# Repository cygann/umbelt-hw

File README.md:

# umbelt-hw

This repo contains the hardware files for Umbelt: a sensory substitution belt
for everyday use. Designed to be worn around the waist underneath any belt,
Umbelt doesn't compromise on function or style. The name Umbelt (pronounced
"oom-belt") is a pun on the German word umwelt, used in English to describe an
organism's sensory environment and perceptions.

Sensory substitution "is a change of the characteristics of one sensory modality
into stimuli of another sensory modality."
([Wikipedia](https://en.wikipedia.org/wiki/Sensory_substitution))
This means that sensory modalities which are not otherwise accessible to an
individual can be recreated using haptic feedback on the waist. This includes
ordinary sensory functions for prosthetic purposes as well as sensory
information that is beyond typical human senses, such as electromagnetic
radiation outside the visible spectrum, the Earth's magnetic field, time,
physical proximity, velocity, or any other information in the computing world.

The initial configuration to try is the compass feature. This maps one's
absolute orientation to the waist by always indicating where north is whenever
the wearer's orientation changes. After wearing this for a while, the wearer
experiences subtle changes in spatial perception. It becomes more natural to
think in terms of absolute orientation, and separate locations become better
integrated into a larger, more continuous sense of space.

# Hardware Design

Umbelt is designed as an assembly of two printed circuits: a rigid printed
circuit board (PCB) and a flexible printed circuit (FPC). The board mounts all
of the electronic components: the microcontroller, power regulators, 13 motor
drivers, integrated sensors (magnetometer, accelerometer/gyroscope, and
microphone), and connectors. The flex PC connects to the board and wraps around
the wearer's waist, providing electrical connections to 12 of the 13 motors.

The Microcontroller is a Raytac MDBT50Q-1MV2 module based on the Nordic nRF52840
bluetooth microcontroller. This bluetooth connection enables phone-based
configuration of Umbelt. A Sparkfun/Adafruit-style Qwiic expansion connector
allows for the daisy-chaining of additional I2C sensors to Umbelt.

Schematics and layout were designed with KiCad version 5.1.10.

Schematics can be found [here](umbelt-board/umbelt-board.pdf).

# Related Repositories

[Software](https://github.com/cygann/umbelt-sw). Haptic effects, sensor
libraries, and user programs.

[Bootloader](https://github.com/cygann/Adafruit_nRF52_Bootloader). This
is a modified version of the Adafruit Feather nRF52840 Sense bootloader, and
that target is to be used when compiling and flashing.

# License

_Creators' note: The aim of this license is to be semi-permissive: Umbelt may
be used in larger projects under different licenses but Umbelt itself and
modifications to it must be open-source under the same license. Refer to license
text for specifics._

Copyright Natalie Cygan and Matthew Pauly 2021.

This source describes Open Hardware and is licensed under the CERN-OHL-W v2 or
later

You may redistribute and modify this documentation and make products
using it under the terms of the CERN-OHL-W v2 (https://ohwr.org/cernohl).
This documentation is distributed WITHOUT ANY EXPRESS OR IMPLIED
WARRANTY, INCLUDING OF MERCHANTABILITY, SATISFACTORY QUALITY
AND FITNESS FOR A PARTICULAR PURPOSE. Please see the CERN-OHL-W v2
for applicable conditions.

Source location: https://github.com/cygann/umbelt-hw

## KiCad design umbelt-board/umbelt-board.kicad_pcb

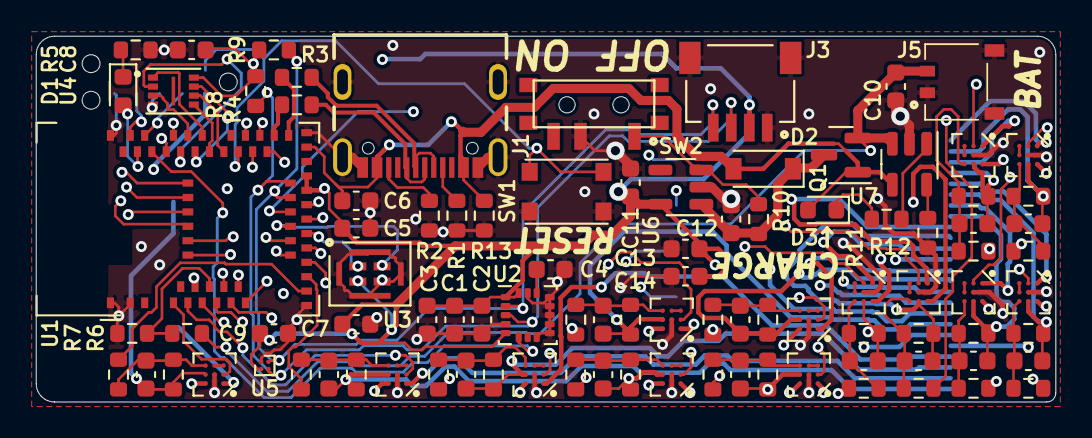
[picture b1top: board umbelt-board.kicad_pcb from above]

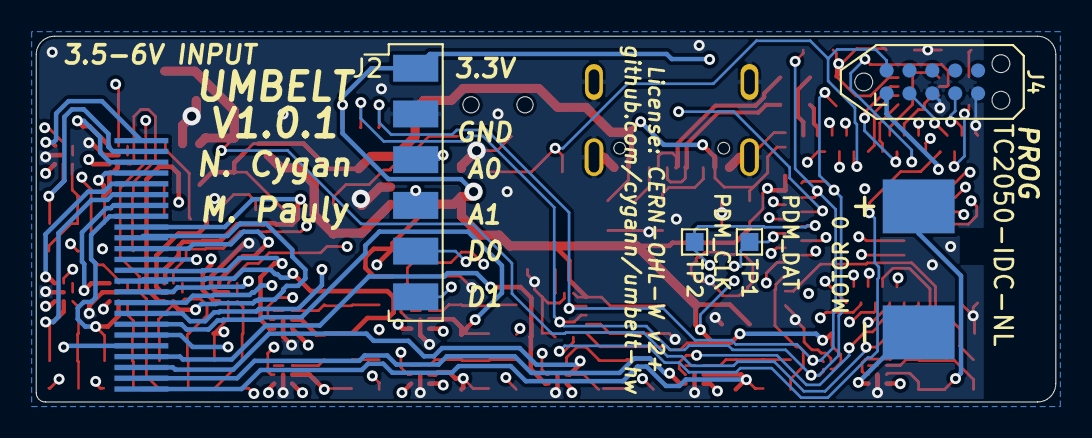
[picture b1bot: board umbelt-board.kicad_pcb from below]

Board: 4 copper layers, 56.6 x 20.3 mm, 101 parts (6 on the bottom side), 115 nets.

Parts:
C1, C7, C8, C14: 0.1uF; C_0603_1608Metric
C2, C15, C16, C17, C18, C19, C20, C21, C22, C23, C24, C25, C26, C27: 4.7nF; C_0603_1608Metric
C3, C9, C13: 2.2uF; C_0603_1608Metric
C4: 0.47uF; C_0603_1608Metric
C5, C6, C10, C11, C12: 10uF; C_0603_1608Metric
D1: SML-D12M1W; LED_0603_1608Metric
D2: MBR0520; D_SOD-123
D3: SML-D12D1W; LED_0603_1608Metric
J1: USB4105-GF-A; GCT_USB4105-GF-A
J2: Conn_01x06; PinHeader_1x06_P2.54mm_Right_Angle_SMD
J3: SM04B-SRSS-TB; JST_SM04B-SRSS-TB(LF)(SN)
J4: TC2050-IDC-NL; Tag-Connect_TC2050-IDC-NL_2x05_P1.27mm_Vertical
J5: BM02B-ACHLKS
J6: Conn_Flex_Motor
J7: Conn_Indiv_Motor
Q1: AO3415A; SOT-23
R1, R2: 5.1k; R_0603_1608Metric
R3, R4: 22; R_0603_1608Metric
R5, R11: 1k; R_0603_1608Metric
R6, R7, R10, R13, R14, R15, R16, R17, R18, R19, R20, R21, R22, R23, R24, R25, R26, R27, R28, R29, R30, R31, R32, R33, R34, R35, R36, R37, R38, R39: 100k; R_0603_1608Metric
R8, R9: 2.2k; R_0603_1608Metric
R12: 10k; R_0603_1608Metric
SW1: KMR231NG-ULC-LFS; KMR2-NG
SW2: CUS-12TB; CUS-12B
TP1: PDM_DAT; TestPoint_Pad_1.0x1.0mm
TP2: PDM_CLK; TestPoint_Pad_1.0x1.0mm
U1: MDBT50Q-1MV2; Raytac_MDBT50Q
U2: ICM-20608; LGA-16_3x3mm_P0.5mm_LayoutBorder3x5y
U3: SPK0641HT4H-1; Knowles_SPK0641HT4H-1
U4: MX25R1635FZUIL0; USON-8_2x3
U5: MMC5633NJL; WLP-4_0.86x0.86mm_P0.4mm
U6: AP7366-33W5; SOT-23-5
U7: MCP73832-2ACI_MC‎; SOT-23-5
U8, U9, U10, U11, U12, U13, U14, U15, U16, U17, U18, U19, U20: DRV8601; BGA-8_3x3_2.1x2.1mm_TI_ZQV

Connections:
+3V3: C1.1, C2.2, C3.1, C5.1, C7.1, C8.1, C9.1, C11.1, C13.1, C14.1, J2.1, J3.2, J4.1, R8.1, R9.1, U1.28, U1.30, U2.1, U2.5, U2.16, U3.4, U4.8, U5.B1, U6.5, U8.A3, U9.A3, U10.A3, U11.A3, U12.A3, U13.A3, U14.A3, U15.A3, U16.A3, U17.A3, U18.A3, U19.A3, U20.A3
/A0: J2.5, U1.10
/A1: J2.6, U1.11
/ACC_IRQ: U1.50, U2.6
/D0: J2.3, U1.48
/D1: J2.4, U1.49
/D+: J1.A6, J1.B6, R4.1
/D-: J1.A7, J1.B7, R3.1
/LED: D1.2, U1.52
/MOTOR_EN_0: U1.4, U20.B1
/MOTOR_EN_1: U1.6, U8.B1
/MOTOR_EN_2: U1.8, U9.B1
/MOTOR_EN_3: U1.12, U10.B1
/MOTOR_EN_4: U1.14, U11.B1
/MOTOR_EN_5: U1.13, U12.B1
/MOTOR_EN_6: U1.7, U13.B1
/MOTOR_EN_7: U1.56, U14.B1
/MOTOR_EN_8: U1.57, U15.B1
/MOTOR_EN_9: U1.58, U16.B1
/MOTOR_EN_10: U1.59, U17.B1
/MOTOR_EN_11: U1.60, U18.B1
/MOTOR_EN_12: U1.61, U19.B1
/MOTOR_PWM_0: R38.1, U1.16
/MOTOR_PWM_1: R14.1, U1.17
/MOTOR_PWM_2: R16.1, U1.18
/MOTOR_PWM_3: R18.1, U1.19
/MOTOR_PWM_4: R20.1, U1.20
/MOTOR_PWM_5: R22.1, U1.21
/MOTOR_PWM_6: R24.1, U1.24
/MOTOR_PWM_7: R26.1, U1.25
/MOTOR_PWM_8: R28.1, U1.26
/MOTOR_PWM_9: R30.1, U1.36
/MOTOR_PWM_10: R32.1, U1.37
/MOTOR_PWM_11: R34.1, U1.38
/MOTOR_PWM_12: R36.1, U1.39
/PDM_CLK: TP2.1, U1.23, U3.2
/PDM_DAT: TP1.1, U1.22, U3.1
/QSPI_CS: U1.44, U4.1
/QSPI_DATA0: U1.43, U4.5
/QSPI_DATA1: U1.47, U4.2
/QSPI_DATA2: U1.46, U4.3
/QSPI_DATA3: U1.45, U4.7
/QSPI_SCK: U1.42, U4.6
/REGIN: C12.2, D2.1, Q1.3, R10.1, U6.1
/RESET: J4.10, SW1.2, U1.40
/SCL: J3.4, R9.2, U1.27, U2.2, U5.A2
/SDA: J3.3, R8.2, U1.29, U2.3, U5.B2
/SWCLK: J4.4, U1.53
/SWDIO: J4.2, U1.51
/USBD+: R4.2, U1.35
/USBD-: R3.2, U1.34
/VDIV: R6.2, R7.1, U1.9
/motor_drivers/OUT+_0: C27.1, J7.1, R39.2, U20.B3
/motor_drivers/OUT+_1: C15.1, J6.1, R15.2, U8.B3
/motor_drivers/OUT+_2: C16.1, J6.3, R17.2, U9.B3
/motor_drivers/OUT+_3: C17.1, J6.5, R19.2, U10.B3
/motor_drivers/OUT+_4: C18.1, J6.7, R21.2, U11.B3
/motor_drivers/OUT+_5: C19.1, J6.9, R23.2, U12.B3
/motor_drivers/OUT+_6: C20.1, J6.11, R25.2, U13.B3
/motor_drivers/OUT+_7: C21.1, J6.13, R27.2, U14.B3
/motor_drivers/OUT+_8: C22.1, J6.15, R29.2, U15.B3
/motor_drivers/OUT+_9: C23.1, J6.17, R31.2, U16.B3
/motor_drivers/OUT+_10: C24.1, J6.19, R33.2, U17.B3
/motor_drivers/OUT+_11: C25.1, J6.21, R35.2, U18.B3
/motor_drivers/OUT+_12: C26.1, J6.23, R37.2, U19.B3
/motor_drivers/OUT-_0: J7.2, U20.A1
/motor_drivers/OUT-_1: J6.2, U8.A1
/motor_drivers/OUT-_2: J6.4, U9.A1
/motor_drivers/OUT-_3: J6.6, U10.A1
/motor_drivers/OUT-_4: J6.8, U11.A1
/motor_drivers/OUT-_5: J6.10, U12.A1
/motor_drivers/OUT-_6: J6.12, U13.A1
/motor_drivers/OUT-_7: J6.14, U14.A1
/motor_drivers/OUT-_8: J6.16, U15.A1
/motor_drivers/OUT-_9: J6.18, U16.A1
/motor_drivers/OUT-_10: J6.20, U17.A1
/motor_drivers/OUT-_11: J6.22, U18.A1
/motor_drivers/OUT-_12: J6.24, U19.A1
GND: C1.2, C2.1, C3.2, C4.2, C5.2, C6.2, C7.2, C8.2, C9.2, C10.2, C11.2, C12.1, C13.2, C14.2, J1.A1, J1.A12, J1.B1, J1.B12, J1.S1, J2.2, J3.1, J3.S1, J4.3, J4.5, J5.1, J5.S1, R1.2, R2.2, R5.2, R7.2, R12.2, R13.2, SW1.1, SW2.2, U1.1, U1.2, U1.15, U1.33, U1.55, U2.4, U2.8, U2.9, U2.10, U2.11, U2.12, U2.13, U2.15, U3.3, U3.5, U3.6, U3.7, U3.8, U4.4, U5.A1, U6.2, U7.2, U8.B2, U9.B2, U10.B2, U11.B2, U12.B2, U13.B2, U14.B2, U15.B2, U16.B2, U17.B2, U18.B2, U19.B2, U20.B2
unnamed: C4.1, U2.14
unnamed: C15.2, R14.2, R15.1, U8.C3
unnamed: C16.2, R16.2, R17.1, U9.C3
unnamed: C17.2, R18.2, R19.1, U10.C3
unnamed: C18.2, R20.2, R21.1, U11.C3
unnamed: C19.2, R22.2, R23.1, U12.C3
unnamed: C20.2, R24.2, R25.1, U13.C3
unnamed: C21.2, R26.2, R27.1, U14.C3
unnamed: C22.2, R28.2, R29.1, U15.C3
unnamed: C23.2, R30.2, R31.1, U16.C3
unnamed: C24.2, R32.2, R33.1, U17.C3
unnamed: C25.2, R34.2, R35.1, U18.C3
unnamed: C26.2, R36.2, R37.1, U19.C3
unnamed: C27.2, R38.2, R39.1, U20.C3
unnamed: D1.1, R5.1
unnamed: D3.1, R11.1
unnamed: J1.A5, R1.1
unnamed: J1.B5, R2.1
unnamed: R10.2, SW2.1, U6.3
unnamed: R11.2, U7.1
unnamed: R12.1, U7.5
unnamed: U8.C1, U8.C2
unnamed: U9.C1, U9.C2
unnamed: U10.C1, U10.C2
unnamed: U11.C1, U11.C2
unnamed: U12.C1, U12.C2
unnamed: U13.C1, U13.C2
unnamed: U14.C1, U14.C2
unnamed: U15.C1, U15.C2
unnamed: U16.C1, U16.C2
unnamed: U17.C1, U17.C2
unnamed: U18.C1, U18.C2
unnamed: U19.C1, U19.C2
unnamed: U20.C1, U20.C2
VBAT: C10.1, J5.2, Q1.2, R6.1, U7.3
VBUS: C6.1, D2.2, D3.2, J1.A4, J1.A9, J1.B4, J1.B9, Q1.1, R13.1, U1.32, U7.4

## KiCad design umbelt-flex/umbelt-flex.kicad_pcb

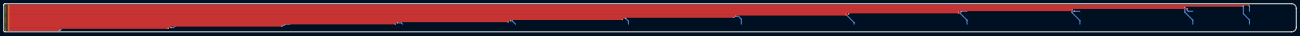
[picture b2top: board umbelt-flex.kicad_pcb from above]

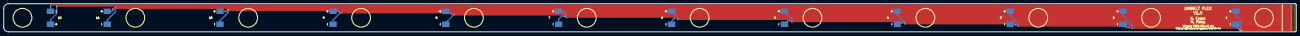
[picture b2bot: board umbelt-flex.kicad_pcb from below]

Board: 2 copper layers, 701.0 x 15.2 mm, 13 parts (12 on the bottom side), 24 nets.

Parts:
J1, J2, J3, J4, J5, J6, J7, J8, J9, J10, J11, J12: Conn_Indiv_Motor
J13: Conn_Flex_Motor

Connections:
/OUT+_1: J1.1, J13.1
/OUT+_2: J2.1, J13.3
/OUT+_3: J3.1, J13.5
/OUT+_4: J4.1, J13.7
/OUT+_5: J5.1, J13.9
/OUT+_6: J6.1, J13.11
/OUT+_7: J7.1, J13.13
/OUT+_8: J8.1, J13.15
/OUT+_9: J9.1, J13.17
/OUT+_10: J10.1, J13.19
/OUT+_11: J11.1, J13.21
/OUT+_12: J12.1, J13.23
/OUT-_1: J1.2, J13.2
/OUT-_2: J2.2, J13.4
/OUT-_3: J3.2, J13.6
/OUT-_4: J4.2, J13.8
/OUT-_5: J5.2, J13.10
/OUT-_6: J6.2, J13.12
/OUT-_7: J7.2, J13.14
/OUT-_8: J8.2, J13.16
/OUT-_9: J9.2, J13.18
/OUT-_10: J10.2, J13.20
/OUT-_11: J11.2, J13.22
/OUT-_12: J12.2, J13.24

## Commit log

2021-07-26 Adds gitignore
2021-07-26 Initial kicad project
2021-08-04 add project local schematic lib, add motor buffers, update gitignore
2021-08-10 add nRF module, SWD connector, flex PCB connector, qwiic connector
2021-08-12 add usb connector, gpio header, pdm microphone, i2c pullups
2021-08-19 add motor driver schematic sheet, footprints for most parts, motion sensor schematic components
2021-08-24 complete schematics and footprints
2021-08-24 pass electrical rules check, annotate schematics, assign all footprints, generate netlist
2021-08-24 add BOM
2021-08-24 Initial commit for umbelt flex pcb
2021-08-24 start layout, tweak some footprints
2021-08-24 Umbelt flex schematics
2021-08-25 Adds .net file for umbelt flex
2021-08-25 more placement, update custom footprints' ref des on fab layer
2021-08-27 add SMD pin header, finished placement
2021-09-08 tweak placement, add text, add test points, add rounded corners
2021-09-10 lots of routing; hard part done
2021-09-17 more routing
2021-09-17 Add license
2021-09-17 fix typo
2021-09-17 add source location to sch and pcb
2021-09-18 complete routing. passes important DRC checks
2021-09-18 tweak ground pours
2021-09-20 complete flex pcb, generate gerbers for both boards
2021-09-26 add exported BOM
2021-10-10 add priced BOM
2021-11-25 update README, add pictures
2021-11-28 add links to bootloader and software repos
2022-01-17 fix SCL/SDA swap on magnetometer, generate outputs

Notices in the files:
umbelt-board/umbelt-board.kicad_pcb:
License: CERN-OHL-W v2+
